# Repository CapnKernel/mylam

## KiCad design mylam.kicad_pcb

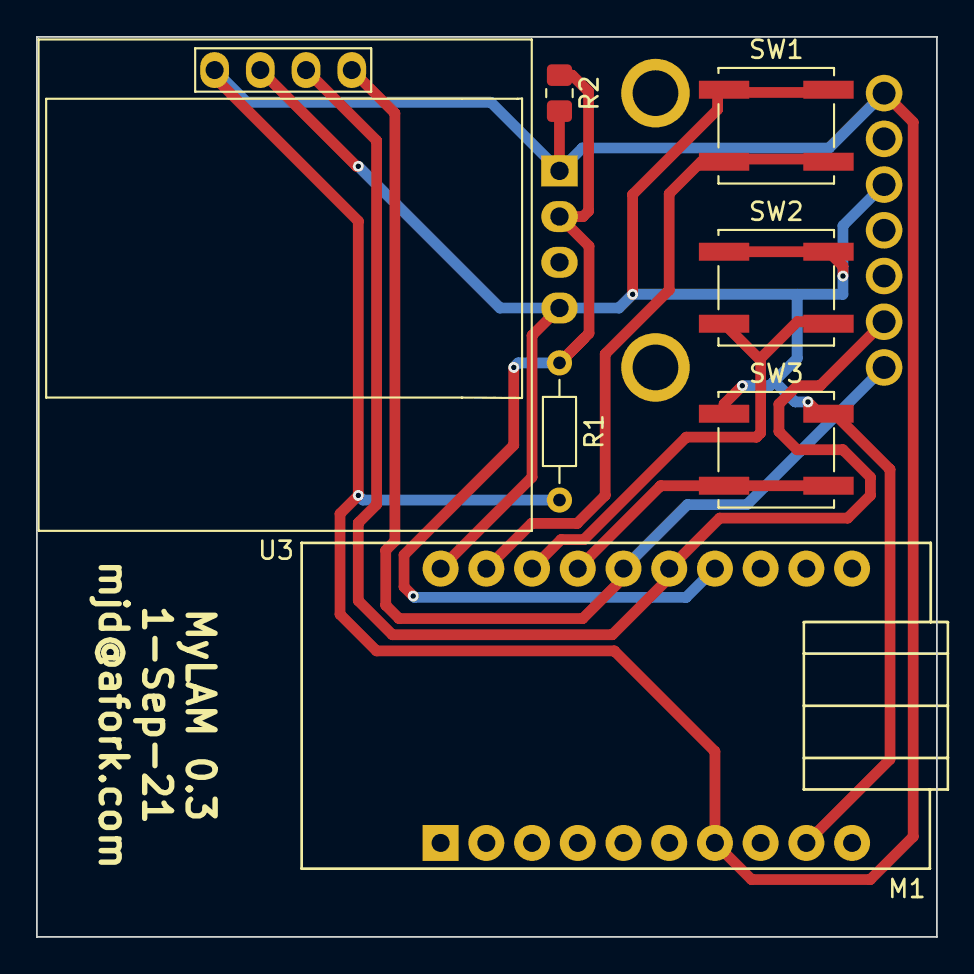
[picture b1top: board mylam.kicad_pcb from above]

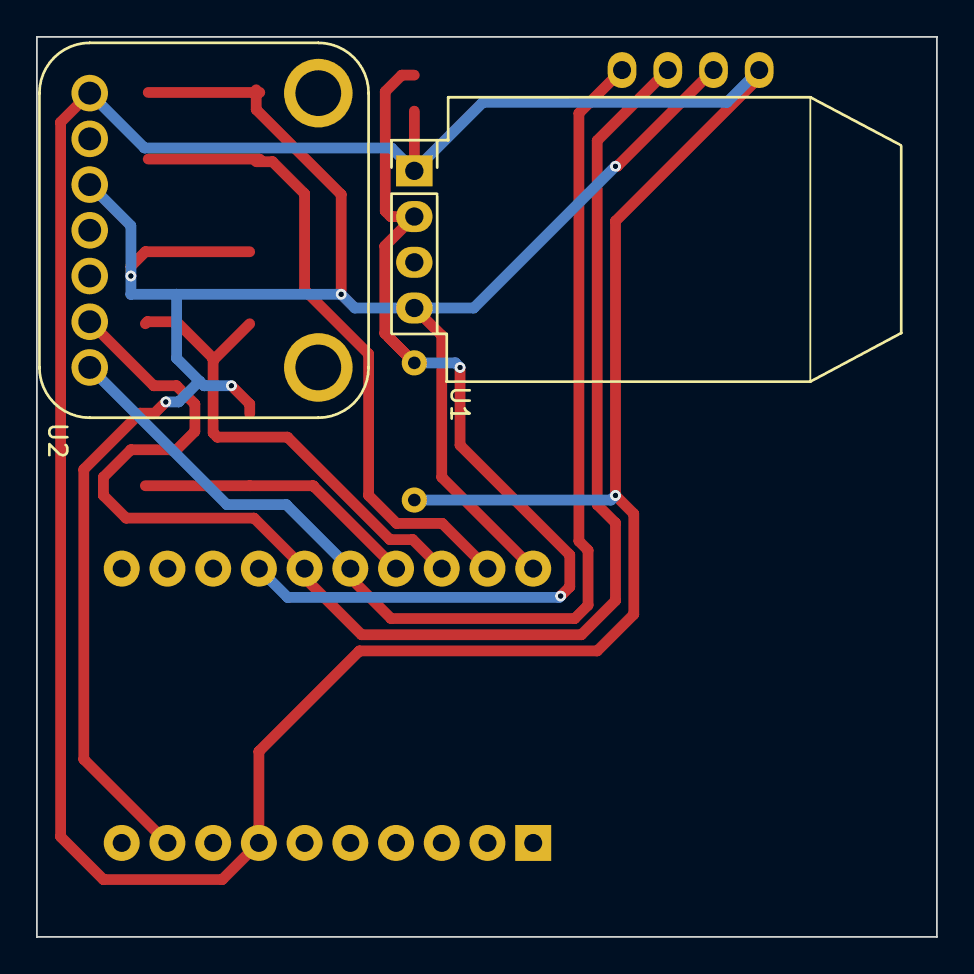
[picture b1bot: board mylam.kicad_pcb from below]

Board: 2 copper layers, 50.0 x 50.0 mm, 9 parts (2 on the bottom side), 8 nets.

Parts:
M1: TINYPICO
R1: 10K; R_Axial_DIN0204_L3.6mm_D1.6mm_P7.62mm_Horizontal
R2: 10K; R_0805_2012Metric_Pad1.20x1.40mm_HandSolder
SW1, SW2, SW3: SW_Push; SW_Push_1P1T_NO_CK_KSC6xxJ
U1: DHT22; DHT22_Temperature_Humidity
U2: VL6180X_Adafruit; VL6180x
U3: SSD1306_OLED_128x32-sensors; 128x64OLED

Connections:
+3V3: M1.7 (V3.3), R1.2, R2.2, U1.1 (VCC), U2.1 (VCC), U3.1 (VCC)
GND: M1.9 (GND), M1.20 (GND), SW1.2, SW2.2, SW3.2, U1.4 (GND), U2.3 (GND), U3.2 (GND)
unnamed: M1.14 (5), R1.1, R2.1, U1.2 (Data)
unnamed: M1.17 (32), SW3.1
unnamed: M1.18 (33), SW2.1
unnamed: M1.19 (RST), SW1.1
SCL: M1.15 (22), U2.6 (SCL), U3.3 (SCL)
SDA: M1.16 (21), U2.7 (SDA), U3.4 (SDA)

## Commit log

2023-11-13 First (and very overdue) commit to git.
